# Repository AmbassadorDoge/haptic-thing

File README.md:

# haptic-thing
Haptic fidget for Hack Club's Solder! 

First time making PCB, might as well make it something I can play with. This is supposed to be a handheld toy where you can tap a membrane and the entire thing will vibrate!

## BOM
- Thin Film Pressure Resistor
- LED
- Haptic Motor
- Battery Holder/Battery
- Resistor(220 ohm)
- Resistor(2k ohm)
- NPN Transistor

## 3D View

Note: Yes, I know that M1 and R1 block the battery holder in the picture, but I'm not actually going to solder the headers on.

## PCB

## Schematic

## Slack
U08F1KG2YFK @doge

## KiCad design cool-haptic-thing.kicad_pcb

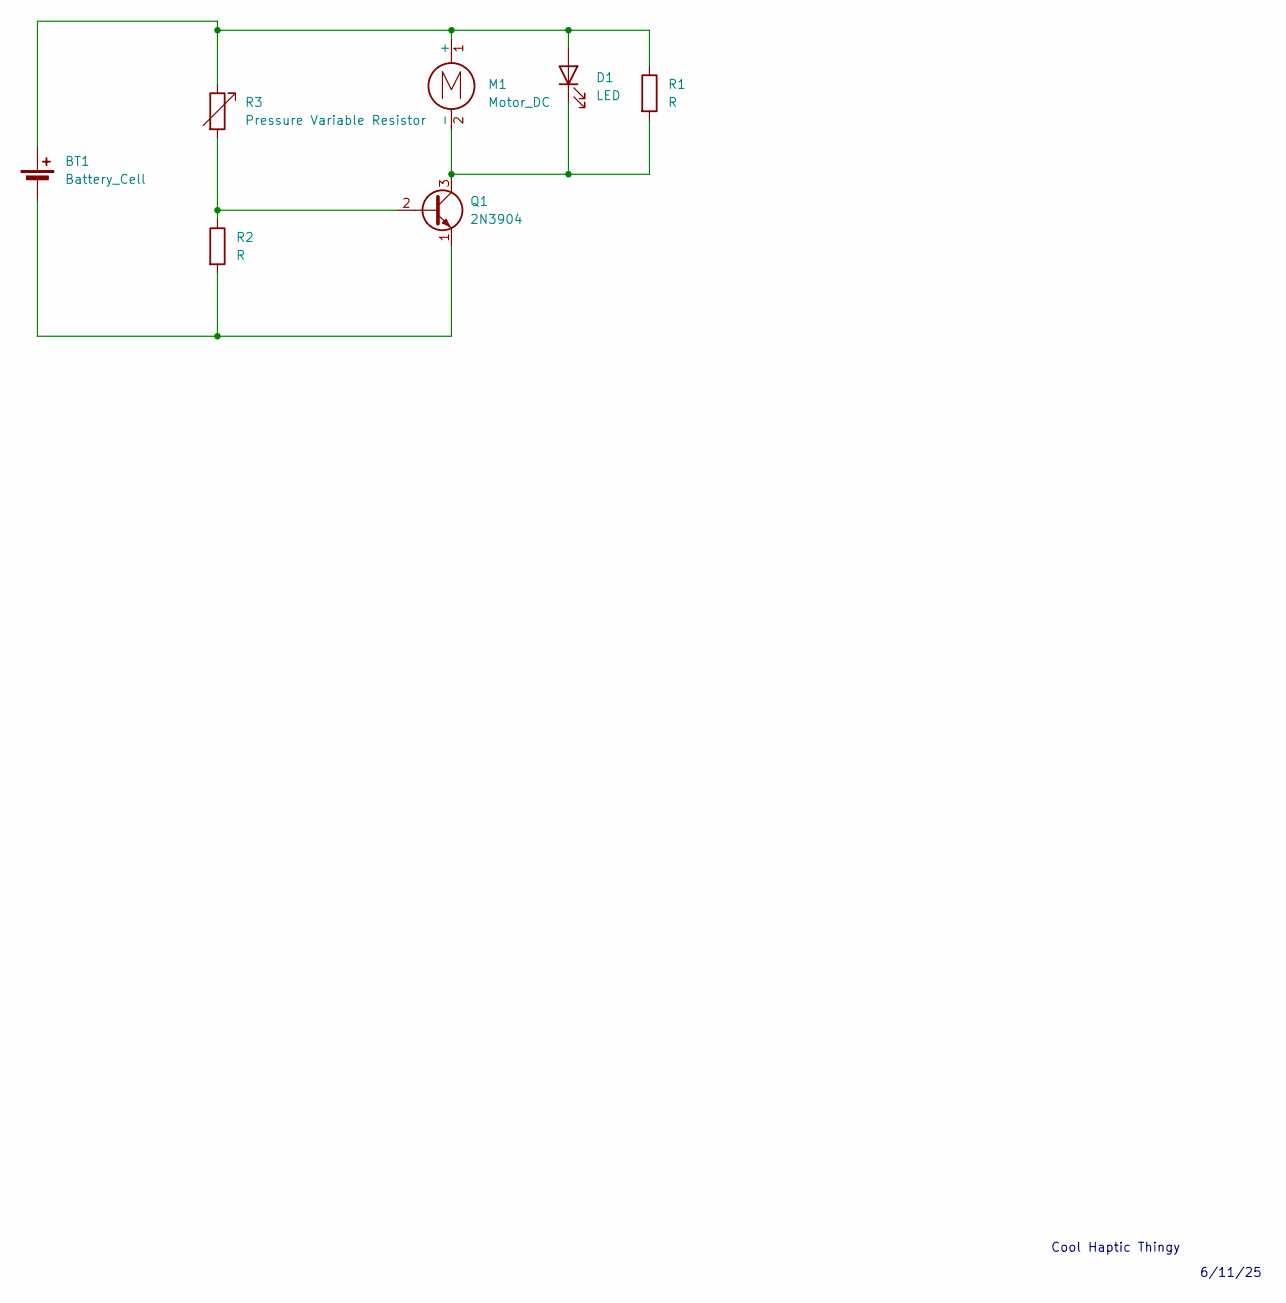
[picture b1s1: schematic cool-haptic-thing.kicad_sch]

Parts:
BT1: Battery_Cell; BatteryHolder_Keystone_3034_1x20mm
D1: LED; LED_D5.0mm
M1: Motor_DC; PinHeader_1x02_P2.54mm_Vertical
Q1: 2N3904; TO-92_Inline
R1: R; PinHeader_1x02_P2.54mm_Vertical
R2: R; R_Axial_DIN0207_L6.3mm_D2.5mm_P7.62mm_Horizontal
R3: Pressure Variable Resistor; PinHeader_1x02_P2.54mm_Vertical

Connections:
unnamed: BT1.1 (+), D1.2 (A), M1.1 (+), R1.1, R3.1
unnamed: BT1.2 (-), Q1.1 (E), R2.2
unnamed: D1.1 (K), M1.2 (-), Q1.3 (C), R1.2
unnamed: Q1.2 (B), R2.1, R3.2

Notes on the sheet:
Cool Haptic Thingy
6/11/25

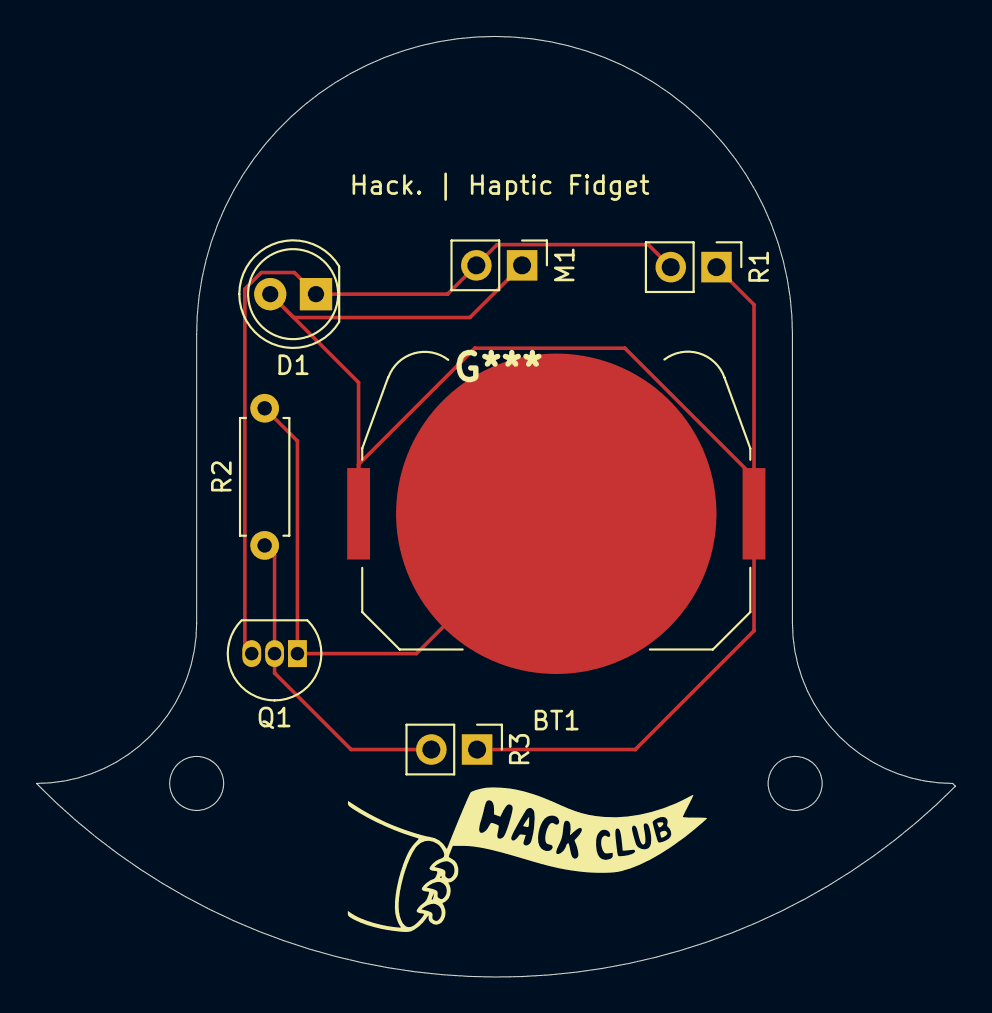
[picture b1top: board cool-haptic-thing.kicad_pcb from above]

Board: 2 copper layers, 51.1 x 52.3 mm, 7 parts (0 on the bottom side), 4 nets.

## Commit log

2025-06-13 Project!
2025-06-13 Readme update
2025-06-15 Update
    ty cyao for the feedback
